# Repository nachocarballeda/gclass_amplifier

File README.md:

# gclass_amplifier
Diseño de un amplificador clase G para la materia Circuitos Electronicos 2. FIUBA

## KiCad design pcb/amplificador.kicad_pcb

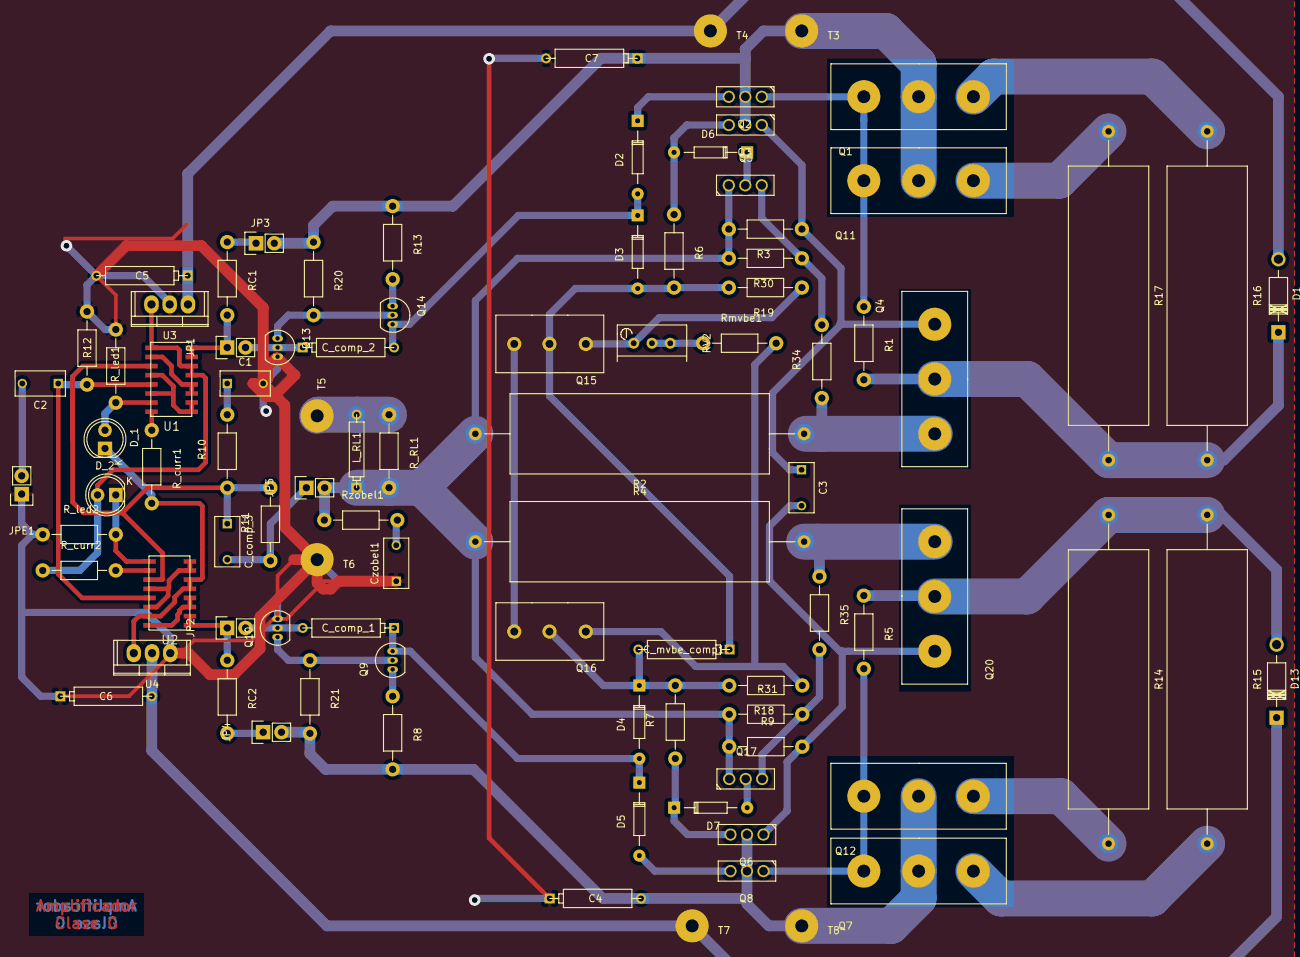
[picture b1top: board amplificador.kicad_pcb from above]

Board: 2 copper layers, 92 parts (0 on the bottom side), 61 nets.

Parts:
C1: 1m; C_Rect_L7_W3.5_P5
C2: 47u; C_Rect_L7_W3.5_P5
C3: 10n; C_Rect_L7_W3.5_P5
C4, C5, C6, C7: 220u; CP5
C_comp_1, C_comp_2: 40p; CP5
C_comp_3: 4p; C_Rect_L7_W3.5_P5
C_mvbe_comp1: 20n; CP5
Czobel1: 100n; C_Rect_L7_W3.5_P5
D1: MBR1645; Diode_DO-41_SOD81_Horizontal_RM10
D2, D5, D6, D7: D1N4148; Diode_DO-35_SOD27_Horizontal_RM10
D3, D4: D1N746; Diode_DO-35_SOD27_Horizontal_RM10
D13: D; Diode_DO-41_SOD81_Horizontal_RM10
D_1, D_2: LED; LED-5MM
JP1, JP2, JP3, JP4, JP5: JUMPER; Pin_Header_Straight_1x02
JPE1: JUMPER; Pin_Header_Straight_1x02
L_RL1: 5u; CP4
Q1, Q4, Q11: 2SC3281; DT-25-B01W-03
Q2, Q3, Q5: MJE340; SOT126_SOT32_Housing_Vertical
Q6, Q8, Q17: MJE350; SOT126_SOT32_Housing_Vertical
Q7, Q12, Q20: 2SA1302; DT-25-B01W-03
Q9, Q10: MPSA42; TO-92_Inline_Narrow_Oval
Q13, Q14: MPSA92; TO-92_Inline_Narrow_Oval
Q15: MJE340; Bornera_Chica
Q16: MJE350; Bornera_Chica
R1, R3, R5, R6, R7, R9: 100R; Resistor_Horizontal_RM10mm
R2, R4: 0R25; Resistor_Ceramic_Horizontal_L36mm-W11mm-H10mm-p45mm
R8, R13: 33R; Resistor_Horizontal_RM10mm
R10: 366R; Resistor_Horizontal_RM10mm
R11, R12: 10k; Resistor_Horizontal_RM10mm
R14, R15, R16, R17: 0R1; Resistor_Ceramic_Horizontal_L36mm-W11mm-H10mm-p45mm
R18, R19: 150R; Resistor_Horizontal_RM10mm
R20, R21: 1K; Resistor_Horizontal_RM10mm
R30: 68R; Resistor_Horizontal_RM10mm
R31, R34, R35: 51R; Resistor_Horizontal_RM10mm
RC1, RC2: 2.4k; Resistor_Horizontal_RM10mm
RV2: POT; Potentiometer_Bourns_3296W_3-8Zoll_Inline_ScrewUp
R_RL1: 10R; Resistor_Horizontal_RM10mm
R_curr1, R_curr2: 820R; Resistor_Horizontal_RM10mm
R_led1, R_led2: 6.8k; Resistor_Horizontal_RM10mm
Rmvbe1: 270R; Resistor_Horizontal_RM10mm
Rzobel1: 10R; Resistor_Horizontal_RM10mm
T3, T4, T5, T6, T7, T8: TORNILLO
U1: MMPQ2222A; SOIC-16
U2: MMPQ2907A; SOIC-16
U3: LM7809CT; TO-220
U4: LM7909CT; TO-220

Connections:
+15: C5.1, D1.2, T4.1, U3.1
+50: C7.1, JP3.2, Q1.2, Q2.2, Q3.2, Q11.2, R13.1, R20.1, T3.1
-15: C6.2, D13.1, T7.1, U4.2
-50: C4.2, JP4.2, Q6.2, Q7.2, Q8.2, Q12.2, R8.2, R21.2, T8.1
Entrada: C2.2, JPE1.2
unnamed: C1.1, R10.2
unnamed: C2.1, R12.2, U1.13, U2.13
unnamed: C3.1, Q3.1, Q4.1, R3.1
unnamed: C3.2, Q6.1, Q20.1, R9.2
unnamed: C_comp_1.1, D4.2, D5.1, Q9.3
unnamed: C_comp_1.2, JP2.2, Q10.2
unnamed: C_comp_2.1, JP1.2, Q13.2
unnamed: C_comp_2.2, D2.2, D3.1, Q14.3
unnamed: C_comp_3.1, R10.1, R11.2, U1.11, U2.11
unnamed: C_comp_3.2, JP5.1, R11.1
unnamed: C_mvbe_comp1.1, D3.2, Q15.2, R6.2, R19.2
unnamed: C_mvbe_comp1.2, D4.1, Q16.2, R7.2, R18.2
unnamed: Czobel1.2, Rzobel1.2
unnamed: D1.1, Q4.2, R1.2, R16.2, R17.2
unnamed: D2.1, Q2.3
unnamed: D5.2, Q8.3
unnamed: D6.1, Q5.2
unnamed: D6.2, Q3.3, R6.1
unnamed: D7.1, Q6.3, R7.1
unnamed: D7.2, Q17.2
unnamed: D13.2, Q20.2, R5.1, R14.1, R15.1
unnamed: D_1.1, R_curr1.2, U2.5, U2.6, U2.15, U4.3
unnamed: D_1.2, R_led1.1, U1.15
unnamed: D_2.1, R_led2.2, U2.9
unnamed: D_2.2, R_curr2.1, U1.5, U1.6, U1.9, U3.3
unnamed: JP1.1, RC1.2, U1.7, U1.8
unnamed: JP2.1, RC2.1, U2.1, U2.2
unnamed: JP3.1, RC1.1
unnamed: JP4.1, RC2.2
unnamed: Q1.1, Q2.1, Q11.1, R1.1
unnamed: Q1.3, R16.1
unnamed: Q4.3, R2.1, R34.1
unnamed: Q5.3, R30.1, R34.2
unnamed: Q7.3, R15.2
unnamed: Q9.1, R8.1
unnamed: Q9.2, Q10.1, R21.1
unnamed: Q11.3, R17.1
unnamed: Q7.1, Q8.1, Q12.1, R5.2
unnamed: Q12.3, R14.2
unnamed: Q13.1, Q14.2, R20.2
unnamed: Q14.1, R13.2
unnamed: Q15.1, Q16.1
unnamed: Q15.3, R19.1, RV2.1
unnamed: Q16.3, R18.1, Rmvbe1.2
unnamed: Q17.3, R31.2, R35.2
unnamed: Q20.3, R4.2, R35.1
unnamed: RV2.2, RV2.3, Rmvbe1.1
unnamed: R_curr1.1, U1.16
unnamed: R_curr2.2, U2.10
unnamed: U1.1, U1.2, U1.12, U1.14
unnamed: U1.3, U1.4, U1.10
unnamed: U2.7, U2.8, U2.12, U2.14
unnamed: U2.3, U2.4, U2.16
Realim: JP5.2, L_RL1.1, Q5.1, Q17.1, R2.2, R3.2, R4.1, R9.1, R30.2, R31.1, R_RL1.2, Rzobel1.1
Salida: L_RL1.2, R_RL1.1, T5.1
SalidaGND: C1.2, C4.1, C5.2, C6.1, C7.2, Czobel1.1, JPE1.1, Q10.3, Q13.3, R12.1, R_led1.2, R_led2.1, T6.1, U3.2, U4.1

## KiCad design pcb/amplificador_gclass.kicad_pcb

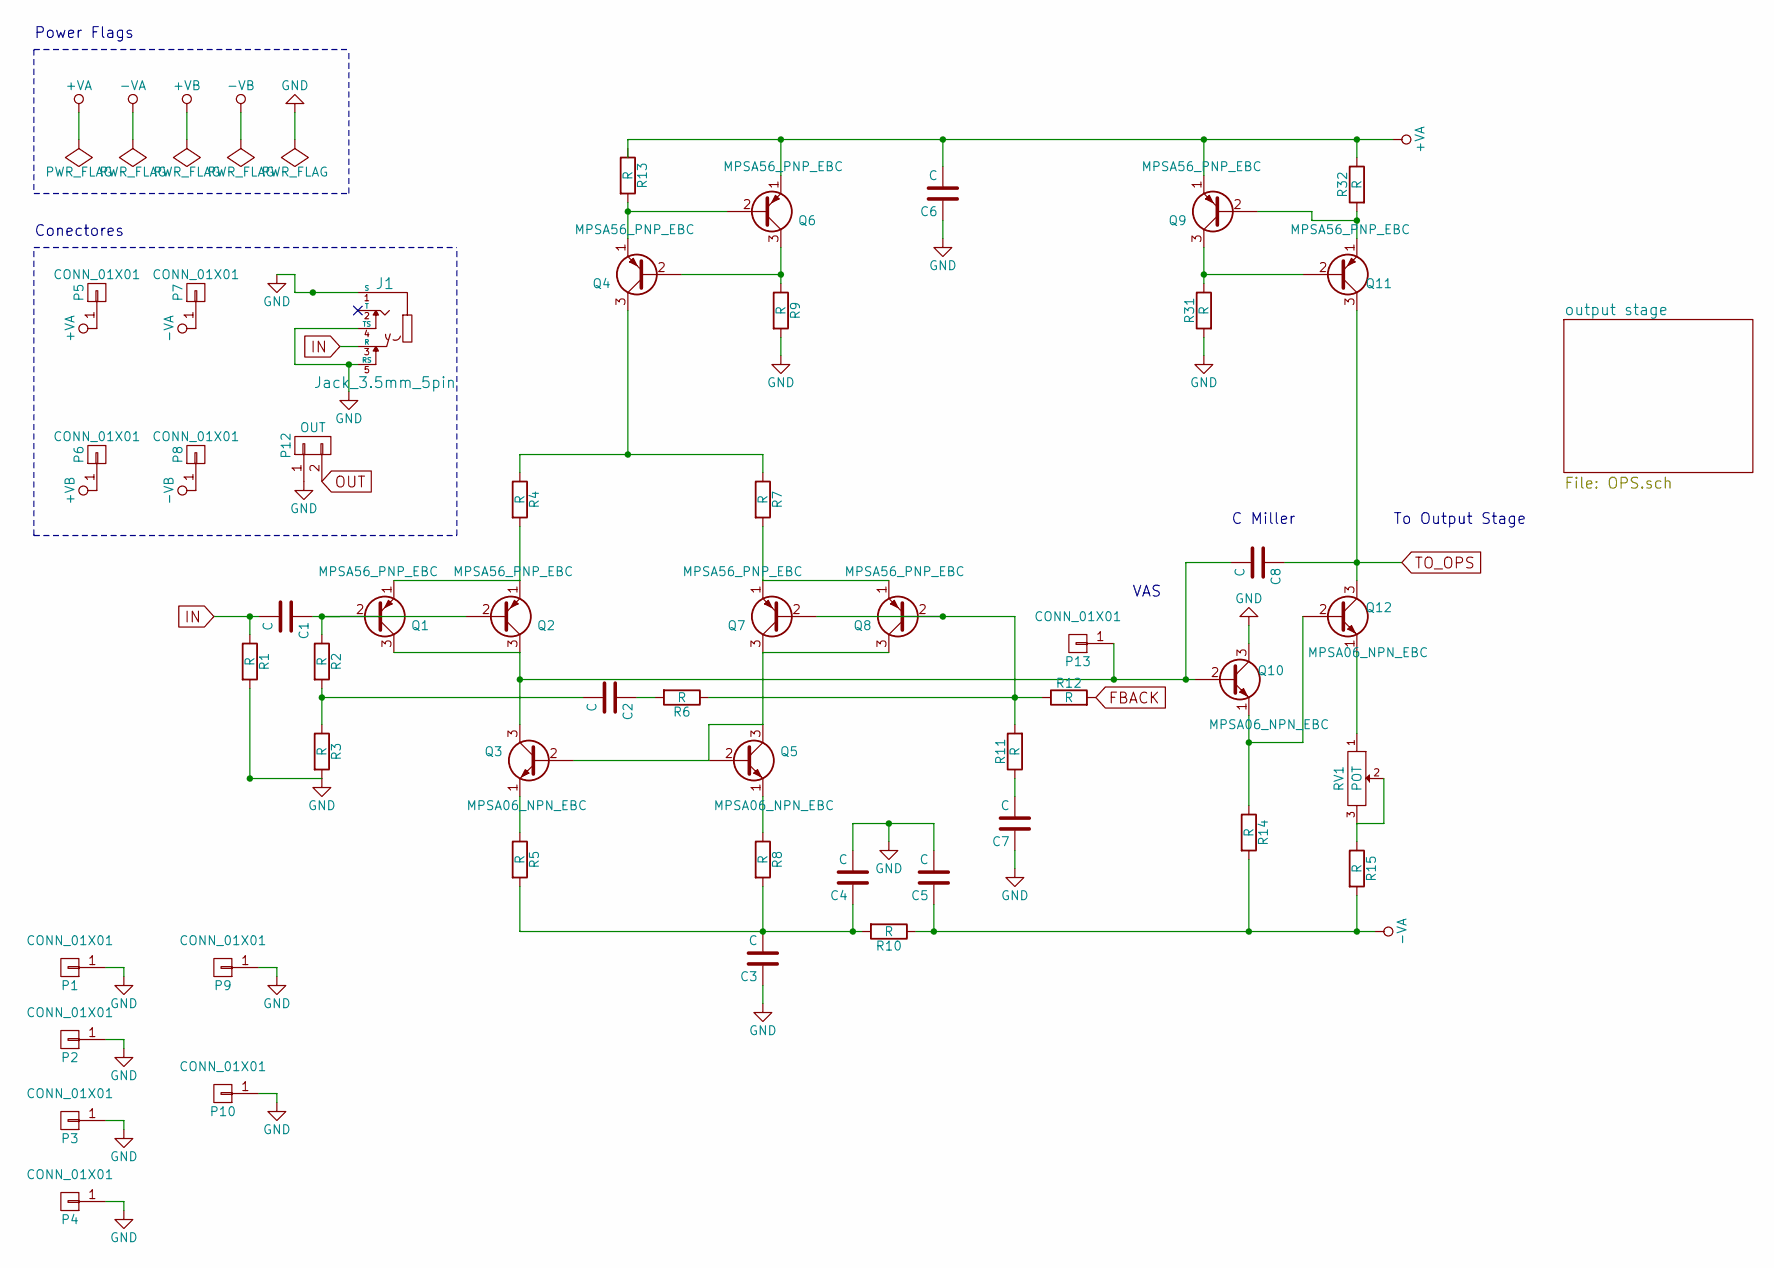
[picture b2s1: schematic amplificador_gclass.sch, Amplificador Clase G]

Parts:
C1, C4, C5: C; Elko_vert_11.2x6.3mm_RM2.5_CopperClear
C2, C3, C6, C7, C8: C; Elko_vert_11.5x8mm_RM3.5
J1: Jack_3.5mm_5pin; jack_puto
P1, P2, P3, P4, P5, P6, P7, P8, P9, P10, P13: CONN_01X01; Pin_Header_Straight_1x01
P12: OUT; Pin_Header_Straight_1x02
Q1, Q2, Q4, Q6, Q7, Q8, Q9, Q11: MPSA56_PNP_EBC; MPSA06-56_TO92_EBC
Q3, Q5, Q10, Q12: MPSA06_NPN_EBC; MPSA06-56_TO92_EBC
R1, R2, R3, R4, R5, R6, R7, R8, R9, R10, R11, R12, R13, R14, R15, R31, R32: R; Resistor_Horizontal_RM10mm
RV1: POT; Pin_Header_Straight_1x03

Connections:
+VA: C6.2, P5.1, Q6.1 (E), Q9.1 (E), R32.1; also elsewhere on the board
+VB: P6.1; also elsewhere on the board
-VA: C5.1, P7.1, R10.1, R14.2, R15.2; also elsewhere on the board
-VB: P8.1; also elsewhere on the board
FBACK: R12.2; also elsewhere on the board
GND: C3.1, C4.2, C5.2, C6.1, C7.1, J1.1 (S), J1.4 (TS), J1.5 (RS), P1.1, P2.1, P3.1, P4.1, P9.1, P10.1, P12.1, Q10.3 (C), R1.2, R3.2, R9.2, R31.2; also elsewhere on the board
IN: C1.2, J1.3 (R), R1.1
unnamed: C1.1, Q1.2 (B), Q2.2 (B), R2.1
unnamed: C2.1, R6.2
unnamed: C2.2, R2.2, R3.1
unnamed: C3.2, C4.1, R5.2, R8.2, R10.2
unnamed: C7.2, R11.1
unnamed: C8.2, P13.1, Q1.3 (C), Q2.3 (C), Q3.3 (C), Q10.2 (B)
unnamed: Q1.1 (E), Q2.1 (E), R4.2
unnamed: Q3.1 (E), R5.1
unnamed: Q3.2 (B), Q5.2 (B), Q5.3 (C), Q7.3 (C), Q8.3 (C)
unnamed: Q4.1 (E), Q6.2 (B), R13.2
unnamed: Q4.2 (B), Q6.3 (C), R9.1
unnamed: Q4.3 (C), R4.1, R7.1
unnamed: Q5.1 (E), R8.1
unnamed: Q7.1 (E), Q8.1 (E), R7.2
unnamed: Q7.2 (B), Q8.2 (B), R6.1, R11.2, R12.1
unnamed: Q10.1 (E), Q12.2 (B), R14.1
unnamed: Q9.2 (B), Q11.1 (E), R32.2
unnamed: Q9.3 (C), Q11.2 (B), R31.1
unnamed: Q12.1 (E), RV1.1
unnamed: R15.1, RV1.2, RV1.3
OUT: P12.2; also elsewhere on the board
TO_OPS: C8.1, Q11.3 (C), Q12.3 (C); also elsewhere on the board

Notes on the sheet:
To Output Stage
VAS
C Miller
Conectores
Power Flags

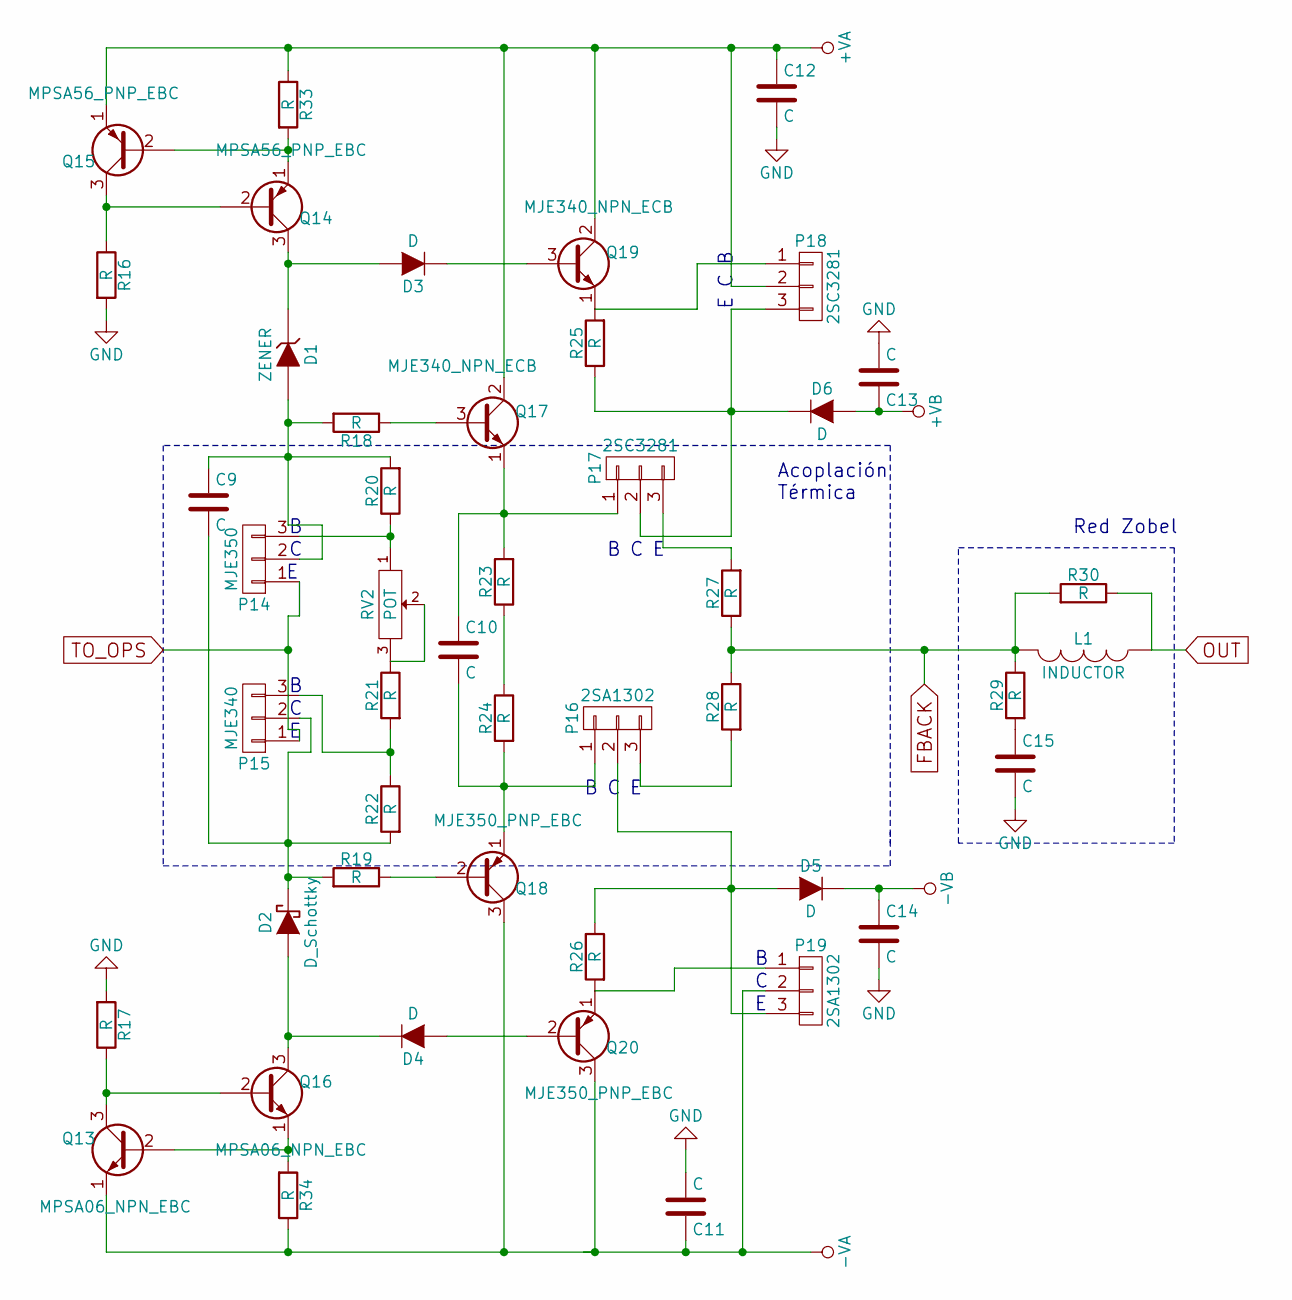
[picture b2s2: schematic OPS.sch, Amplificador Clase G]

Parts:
C9, C10, C11, C12, C13, C14, C15: C; Elko_vert_11.5x8mm_RM3.5
D1: ZENER; Diode_DO-35_SOD27_Horizontal_RM10
D2: D_Schottky; Diode_DO-35_SOD27_Horizontal_RM10
D3, D4, D5, D6: D; Diode_DO-35_SOD27_Horizontal_RM10
L1: INDUCTOR; Resistor_Horizontal_RM10mm
P14: MJE350; bornera_chica
P15: MJE340; bornera_chica
P16, P19: 2SA1302; bornera_grande
P17, P18: 2SC3281; bornera_grande
Q13, Q16: MPSA06_NPN_EBC; MPSA06-56_TO92_EBC
Q14, Q15: MPSA56_PNP_EBC; MPSA06-56_TO92_EBC
Q17: MJE340_NPN_ECB; TO-220_Neutral123_Vertical
Q18: MJE350_PNP_EBC; TO-220_Neutral123_Vertical
Q19: MJE340_NPN_ECB; MJE340_gclass
Q20: MJE350_PNP_EBC; MJE_350_gclass
R16, R17, R18, R19, R20, R21, R22, R23, R24, R25, R26, R29, R30, R33, R34: R; Resistor_Horizontal_RM10mm
R27, R28: R; RESIST_35MMX10MM
RV2: POT; Pin_Header_Straight_1x03

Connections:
+VA: C12.1, P18.2, Q15.1 (E), Q17.2 (C), Q19.2 (C), R33.1; also elsewhere on the board
+VB: C13.1, D6.2 (A); also elsewhere on the board
-VA: C11.1, P19.2, Q13.1 (E), Q18.3 (C), Q20.3 (C), R34.1; also elsewhere on the board
-VB: C14.1, D5.1 (K); also elsewhere on the board
FBACK: L1.2, R27.1, R28.1, R29.1, R30.2; also elsewhere on the board
GND: C11.2, C12.2, C13.2, C14.2, C15.2, R16.2, R17.2; also elsewhere on the board
unnamed: C9.1, D1.2 (A), P14.2, R18.2, R20.2
unnamed: C9.2, D2.1 (K), P15.2, R19.2, R22.2
unnamed: C10.1, P17.1, Q17.1 (E), R23.2
unnamed: C10.2, P16.1, Q18.1 (E), R24.2
unnamed: C15.1, R29.2
unnamed: D1.1 (K), D3.2 (A), Q14.3 (C)
unnamed: D2.2 (A), D4.1 (K), Q16.3 (C)
unnamed: D3.1 (K), Q19.3 (B)
unnamed: D4.2 (A), Q20.2 (B)
unnamed: D5.2 (A), P16.2, P19.3, R26.1
unnamed: D6.1 (K), P17.2, P18.3, R25.1
unnamed: P14.3, R20.1, RV2.1
unnamed: P15.3, R21.2, R22.1
unnamed: P16.3, R28.2
unnamed: P17.3, R27.2
unnamed: P18.1, Q19.1 (E), R25.2
unnamed: P19.1, Q20.1 (E), R26.2
unnamed: Q13.2 (B), Q16.1 (E), R34.2
unnamed: Q13.3 (C), Q16.2 (B), R17.1
unnamed: Q14.1 (E), Q15.2 (B), R33.2
unnamed: Q14.2 (B), Q15.3 (C), R16.1
unnamed: Q17.3 (B), R18.1
unnamed: Q18.2 (B), R19.1
unnamed: R21.1, RV2.2, RV2.3
unnamed: R23.1, R24.1
OUT: L1.1, R30.1; also elsewhere on the board
TO_OPS: P14.1, P15.1; also elsewhere on the board

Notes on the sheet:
Acoplación Térmica
Red Zobel

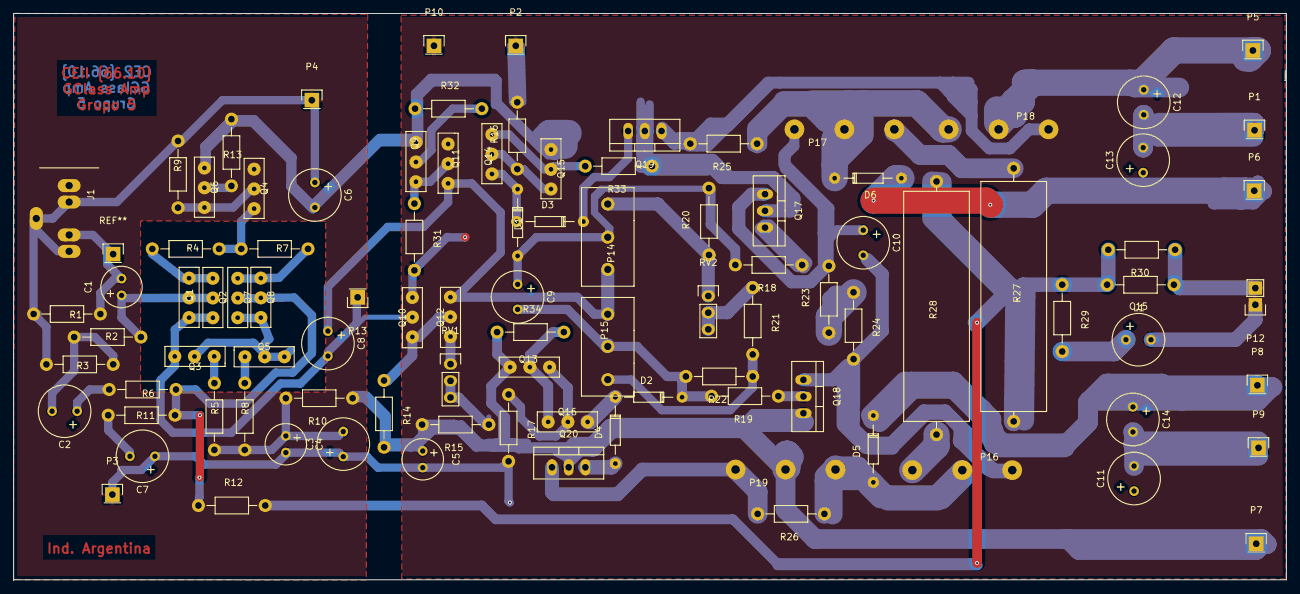
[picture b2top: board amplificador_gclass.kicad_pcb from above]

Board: 2 copper layers, 193.7 x 86.2 mm, 97 parts (0 on the bottom side), 54 nets.

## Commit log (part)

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2015-04-29 Agrego archivos iniciales al repo.
2015-05-08 cambio nombre de carpeta.
2015-05-08 Agrego algunas simulaciones.
2015-05-08 Edito simulaciones, agrego .gitignore
2015-05-08 modified: .gitignore new file: informe/caratula.tex new file: informe/documento.pdf new file: informe/documento.tex new file: informe/fiuba.pdf
2015-05-09 agrego archivos
2015-05-21 closes #1 , averiguados todos los transistores, esperando cotizacion de electronica liniers
2015-05-21 Creo esquematico en kicad del amplificador, falta arreglar un par de errores que tira GND , ya me habia pasado, preguntar que onda. Despues queda hacer bien el netlist sabiendo que componentes vamos 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
2015-05-21 Agrego alguna info al readme
2015-05-22 Sigo con el fucking error de power conectors...
2015-05-22 Problema sobre power conections arreglado, ahora hay otros quilombos, creo que tiene que ver con el encapsulado de los transistores.
2015-06-01 Sigo trabajando en el PCB usando Kicad, necesito mas info sobre los diodos para continuar.
2015-06-04 Agrego algunos datasheets, el export kicad en pdf y sigo trabajando en el PCB
2015-06-05 Termino la primera version del PCB para el amplificador, queda engordar las pistas que llevan alta corriente.
2015-06-08 Arreglo problema, se mostraba cobre en el front , solo lo hice para Q1, queda hacerlo en todos y ajustar bien los drills, acorde a los que existen en el LCI...
2015-06-08 Agrego simulacion ampli G
2015-06-08 Cambio footprints, empiezo a re-rutear
2015-06-09 nacho la soba
2015-06-09 ultimos avances falta poco para terminar
2015-06-10 pcb casi listo
    el pcb esta casi listo
2015-06-10 doc de prueba
2015-06-10 agrando la mayoria de las pistas, alejo algunas pistas criticas del borde, exporto archivos de fabricacion.
2015-06-10 Faltó cerrar el programa antes de pushear :P...
2015-06-11 exporto archivos para LCI
2015-06-11 cambios
2015-06-11 ahora si terminado
2015-06-22 Arreglando PCB
2015-06-22 Cambio las fuentes de corrientes por unas mas estables, agrando todas las pistas, agrego mini planos de tension para potencia, cambio pines de salida.
2015-06-22 Arreglo un par de cositas mas, creo que con esto ya etsamos.
2015-06-22 Agrego nuevos edges.
2015-06-22 cambios minimos.
2015-06-23 Agrando mucho mas las pistas, agrego pin de entrada, muevo diodo zener
2015-06-23 Pistas MAS grandes, export archivos, arreglo pequeños defectos
2015-06-24 pcb disipadores
2015-07-02 cambio una cosa
2015-07-02 algun cambio
2015-07-03 agrego simulacion de error
2015-10-26 Agrego todo lo que tenia del informe en sharelatex.
2015-10-26 elimino pdf.
2015-11-07 subo el pdf del informe para que lo pueda ver Fede, y muevo modelos
2015-11-07 2 asc del gdrive al repo
2015-11-08 agrego simulaciones
    agrego varias simulaciones del circuito final con la configuracion de
    entrada con doble par diferencial y tension de +/- 15V
2015-11-08 cambie los nombres de los archivos
2015-11-16 to-do
2015-11-30 Trabajando con THS4532
    Agrego Footprint y model hecho a mano del THS.
    Agrego modelo Spice THS (ver si funca).
    Agrego el informe main.pdf asi Fede lo puede ver.
2015-11-30 Ordenando Repo
    Renombro carpetas que contenian espacio.
    Muevo carpetas a donde corresponden.
    PCB.PRETTY queda en su lugar para evitar problemas con rutas KiCad.
2015-11-30 Limpio, agrego cosas
    Agrego carpeta aparte para ampli usando THS.
    Agrego datasheet de THS4532.
    Odeno capeta simulaciones.
2015-11-30 Agrego simulacion y pdf
    Agrego primera simulacion del modulo THS4532 de Texas. La misma usa un modelo hecho por la gente de TI.
    Agrego documento de TI que trata sobre amplificadores diferenciales.
2015-11-30 Arranco sch para full diff
2015-11-30 Trabajando con THS4532
    Agregada simulacion que prueba integrado. (success)
    Agregada simulacion que prueba GCLASS with THS. No puede simular, tarda mucho.
2015-12-03 Verifiqué las simulaciones, la posta es el Clase G par doble +15-15.asc
2015-12-04 Avance con el informe de avance, falta agregar a Rui, y su padrón.
    Falta un punto que no entendí que es lo que quiere que pongamos, y estaría bueno que lean revisen opinen y modifiquen.
2015-12-04 Argegado rui a la caratula
2015-12-04 agregue fiuba.pdf para que compile
2015-12-04 Agregue pdf de la charla de diseño de circuitos integrados, por si nos ayuda a entender que quieren del informe de avance
2015-12-04 huevadas menores
2015-12-04 Agregué el último diseño del circuito en el directorio "impreso"
2015-12-04 pendientes a txt aparte
2015-12-04 Agregue pdf que explica lo que hay que chamullar. VERLO
2015-12-04 lalala
2015-12-04 LALALAgst (agregue al informe algunas sims)
2015-12-04 especificaciones tomadas del informe anterior
2015-12-04 distorsion papelon lalala
2015-12-04 un par de notebooks que use para hacer cuentitas
2015-12-05 1er informe de avance
2015-12-06 muevo informe a carpeta informe-viejo
2015-12-06 Abro carpeta del informe final
2015-12-07 resistencias in y out
2015-12-07 Habia elegido mal las pags del capitulo del douglas
2015-12-09 circuito que mandó por mail Fede
2015-12-09 sims
2015-12-09 baje a 71.5 las re de vas
2015-12-09 nuevos graficos de barridos de r_out con fuente de corriente a la salida
2015-12-10 datasheets
2015-12-11 no creo haber cambiado nada en el informe pero git dice que sí, así que acá va commit
2015-12-11 circuito de doble emisor común como vas que sugirio fede
2015-12-11 simulaciones crap incompletas
2015-12-11 mas de lo mismo
2015-12-11 huevada
2015-12-11 Calculo de disipadores
    Falta poner un chamuyo de como se calcula el caso de maxima disipacion, preguntar que pasa con varios transistores en un mismo disipador y ver porque da negativo el calculo para la parte interna de l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
2015-12-11 circuitos para el 2do informe de avance
2015-12-11 un poco de informe de avance
2015-12-12 correciones fede
    Agrego simulacion con correcciones de fede.
    Edito TODO.
2015-12-12 closes #7 #6 #5 #4 #3 #2 Ordeno cosas, arreglo to-do
2015-12-12 Varios closes
    closes #6
    closes #5
    closes #4
    closes #3
2015-12-12 closes #2
2015-12-13 New Components & Footprints
2015-12-13 Agregado el amplificador final para el informe
    Este es un mensaje descriptivo.
    En esta oportunidad, les vengo a ofrecer un archivo de LTSpice,
    extensión asc, que conjuga el fruto de nuestros esfuerzos hasta la
    fecha, menos nuestros olvidos y errores. Sin esos subcircuitos tan
    odiados por Iván, esta versión ofrece una distorsión 4 veces mayor a la
    especificada, culpa de una pérdida importante de ganancia de lazo en la
2015-12-14 Terminado el esquemático armado a partir de ampli-exp.asc, empiezo el PCB.
2015-12-14 Regenerados los gráficos del informe de avance
    Regenerados los gráficos que ya había y alguna cosita más. Pero,
    faltaría en grueso de las cosas que nunca hubo, pero me parece que es
    poca cosa. En particular, no hay nada escrito respecto del diseño del
    circuito, salvo el resultado final.
    También, se agrega un .mod con los modelos de spice que me había
    olvidado de subir, y algunos datos sacados de ltspice de simulaciones.
2015-12-14 Agrego info al asc
    Esto es para facilitar un posible debug. Saludos para anojo.
2015-12-14 Esta casi listo el PCB, necesito ayuda, ensanchen las pistas de potencia, pongan un plano de masa atrás, para vincular todos los componentes que falta mandar a masa, y hacen falta un par de vías.
    Con más tiempo, lo dejaría mejor, pero es un quilombo. Tendría que comparar como hice la vez pasada, que me quedó de re chupete.
2015-12-14 Avances en el informe
    Chamullos de compensación y diseño de las primeras
    2 etapas. También, simulaciones de ganancia de estas etapas.
    Fixes #20
2015-12-14 Terminé la versión 0.1 del PCB. Listo? Aprobamos el informe de avance?
2015-12-15 ashitoen
2015-12-15 Editando informe
    AHHHHHHHHHHHHHHHH!!!
2015-12-15 Agregando exports de PCB
    ya casi estamos.
2015-12-15 Selecciono y agrego fotos de los disipadores
2015-12-15 Corrijo potncia en diagrama
2015-12-15 ashoten
2015-12-15 edito informe
2015-12-15 Final de cursada
2015-12-15 first
2015-12-15 yeah
2015-12-15 Stuff
2015-12-16 Agregué la Red de Zobel.
2015-12-16 Agregué el punto de Red de Zobel en el informe.
2015-12-16 Agrego BOM, script que la genera y tutorial
2015-12-16 BOM: digo cuales son SMD, queda definir segundo disipador
2015-12-16 Arreglo calculos disipador, lo cambio y edito lista
2015-12-16 Arreglo disipadores. pongo ZD14
    tambien edito lista de componentes..
2015-12-16 Teminamos la BOM
    closes #17
2015-12-16 elimino lo que se dijo del clase D
2015-12-16 Exporto el nuevo PCB y lo pongo en el tex
    Y ahi va otro issue.
    closes #18
2015-12-16 Agrego materiales de las cosas
2015-12-16 Edito Tex
    Agrego cosas a realizar en febrero y datos de fuente conmnutada
2015-12-16 Trabajando en integracion
    Armo diagramas de coneccionado completo e interno.
    Agrego modelo 3D del PCB para futuras imagenes de integracion con mas realismo.
2015-12-17 Agregué texto a la descripción de las etapas, especificando los motivos de la elección de las distintas opciones de diseño.
2015-12-17 meto chamuyo de integracion
2015-12-17 asht
2015-12-17 Ordeno secciones
2015-12-17 Agregué la explicación de la realimentacion por bloques.
2015-12-17 Cosas. No me acuerdo
2015-12-17 Capacitancias en cables
    Meto chamuyo, tiro footnote al paper.
    Pongo imagen de cable trenzado forrado que es la posta.
    Explico que somos muy grosos haciendo PCBs.
2015-12-17 Agregué resistencias de emisor, y resistencia a la salida. No pude agregar inductor, no lo encuentro en las bibliotecas.
2015-12-17 eesssaa
2015-12-17 Agregué el texto como pidio Nachito.
2015-12-17 inductor
2015-12-17 un poco de un par de cosas
2015-12-17 Agregué el separador de capacitancia de carga al esquemático y al PCB.
2015-12-17 lololo
2015-12-17 el circuito nuevo
2015-12-17 Redes de Salida
    Red zobel + R-L
    Chamuyo, simulacion y mas.
2015-12-17 Agregué el diagrama de compensación ideal, y un poco de texto.
2015-12-17 antecedentes.. o algo asi
2015-12-17 Expliqué porqué usamos las fuentes de corriente que usamos, y los reguladores de 9V.
2015-12-17 Agregué cómo calcular el Slew-Rate, Bertu-Style.
2015-12-17 Haciendo algunas modificaciones y restructurando fiero
2015-12-17 mas retoques
2015-12-17 un poco mas
2015-12-17 detalle
2015-12-17 Se mandó reentrega informe avance final
2015-12-17 Ordeno y limpio Repo
2016-03-15 Cambiando modelos transistores entrada
    Ahora los transistores de la simulacion son los que vamos a utilizar (integrados)
    closes #44
2016-03-15 ashtast
2016-03-15 arrancando con protecc
2016-04-19 Revert "detalle"
    This reverts commit b4a9fcb8eccff1bf00586a25a69ab8f41817f76b.
2016-04-19 Revert "un poco mas"
    This reverts commit 4aeb702aca40b6e1d13bc07876453ab2d322e19a.
    Conflicts:
    avance_de_proyecto/img/realimentacion-global.png
2016-04-19 Revert "Revert "un poco mas""
    This reverts commit 7625ee5e7ec98d5bfb874bc8b2bc53a13fd7c74d.
2016-04-19 Revert "Cambiando modelos transistores entrada"
    This reverts commit 5f070beb9ecd4bbab59de4c331594395f4f89d66.
2016-04-19 Revert "Ordeno y limpio Repo"
    This reverts commit d58d696824c45bbce0f2da3025cfa9f12b55e583.
2016-05-10 Modifiqué los transistores de la etapa diferencial. Última versión: ampli-exp.asc
2016-06-13 Agregué 2 archivos de simulaciones, en los que probamos las protecciones para el circuito.
2016-07-01 agrego documento copado de protecciones
2016-09-23 Se hizo el ruteo con los nuevos componentes, y se corrigieron los valores de las protecciones, corrigiendo las disparidades.
    Ya se mandó el circuito al LCI, para hacer.
2017-02-20 Ensanché las vías del PCB y agregué un par de vías.
2017-06-16 fist
2017-06-22 cleanup
2017-06-22 ahst
2017-07-27 Minor changes
    *KiCad BRD file: A fucking component's label was moved in ordeer to allow a better understanding of the board.
    *Ampli-exp.asc & primera-etapa.asc Power sources +12/-12 replace old & stupid voltage divider.
2017-08-08 ashtgagas
2017-08-09 cambios rui
2017-08-09 shtap
2017-08-10 ashtg
2017-08-10 shtpun
2017-08-10 astas
2017-08-11 ashtapdun
2017-08-11 asgdg
2017-08-12 adtgaprd
2017-08-17 ashg
2017-08-18 ardpun
2017-08-18 agpuanw
2017-08-19 ashtad
2017-08-19 doanpd
2017-08-23 oeshtn
2017-08-25 shtoe
2017-08-25 ashtptsh
